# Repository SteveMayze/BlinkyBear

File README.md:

# BlinkyBear
This is a small case-study in creating a custom board layout with KiCad. A small writeup can be found on my  [Contextual Electronics Build Log](https://forum.contextualelectronics.com/t/steves-build-log/28/62) until I get around to writing things up better here.

The BOM is simple enough, 

* 1 x CR 1216, CR 1220 Horizontal Surface mount battery holder
* 1 x Mini Slide Switch e.g. SK12C0405SG1.5RT
* 2 x 1556769 RGB LED (EAN: 2050004827125) or similar
* 1 x Brooche pin, 15mm

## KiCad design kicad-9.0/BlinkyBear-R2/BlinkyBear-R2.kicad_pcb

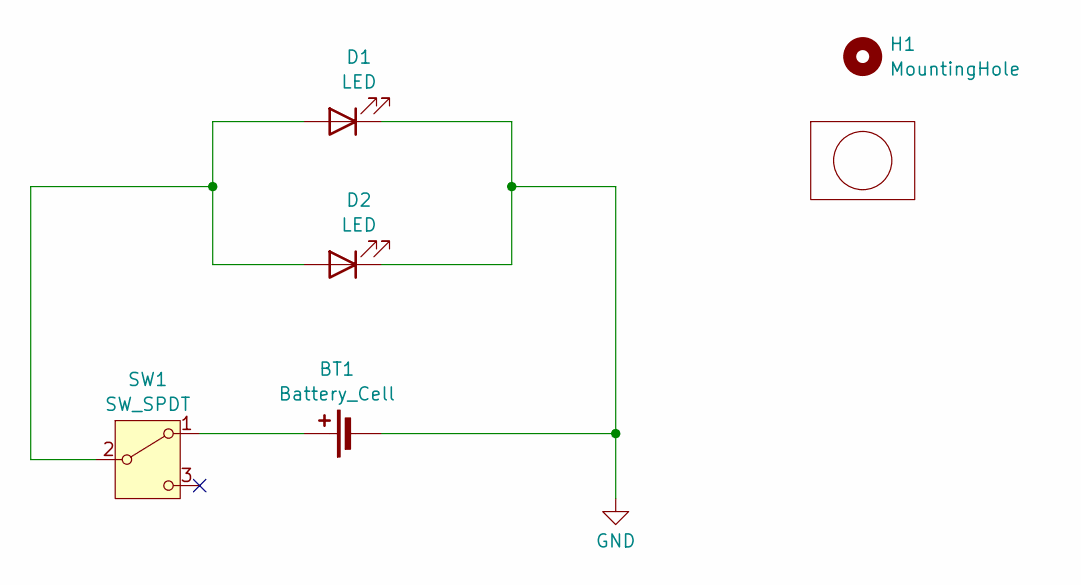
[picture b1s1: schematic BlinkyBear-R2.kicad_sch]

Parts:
BT1: Battery_Cell; CR1220_Halter
D1, D2: LED; LED_D5.0mm
H1: MountingHole; Butterfly-Pin
Lg1: logo; ZAM_LOGO_440
SW1: SW_SPDT; SW_SPDT_PCM12

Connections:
GND: BT1.2 (-), D1.1 (K), D2.1 (K)
unnamed: BT1.1 (+), SW1.1 (A)
unnamed: D1.2 (A), D2.2 (A), SW1.2 (B)

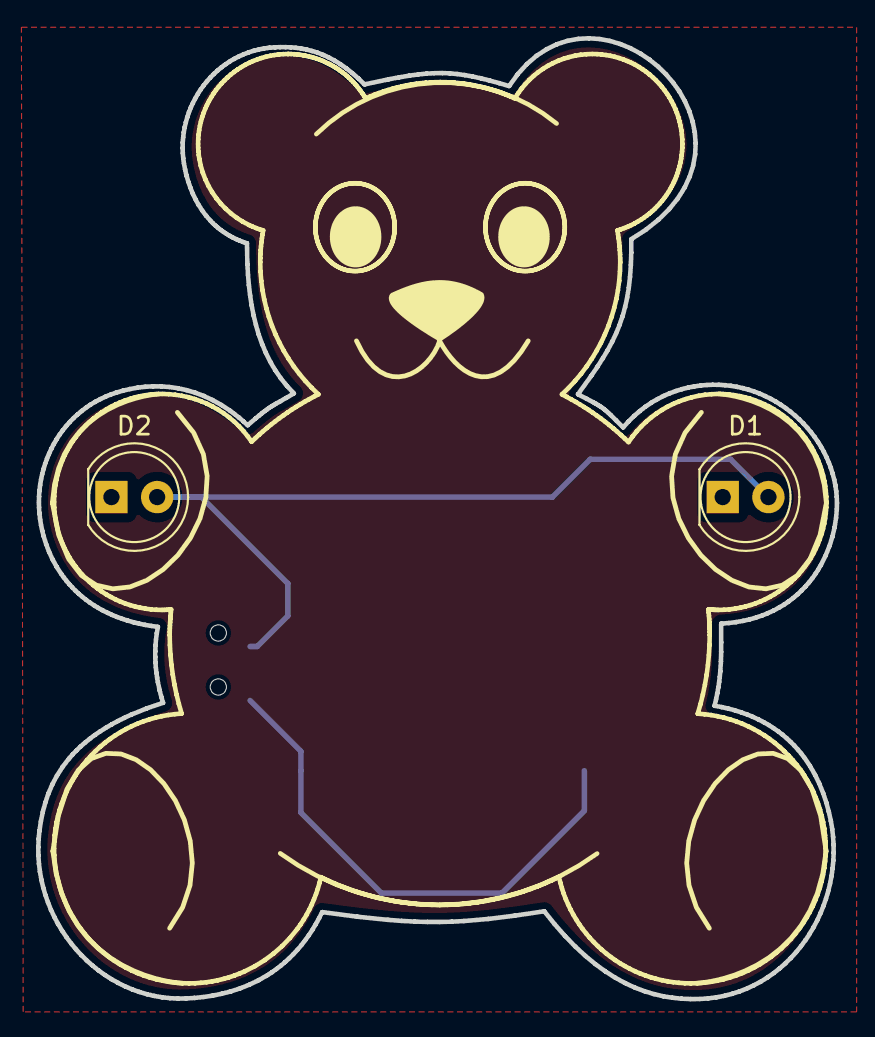
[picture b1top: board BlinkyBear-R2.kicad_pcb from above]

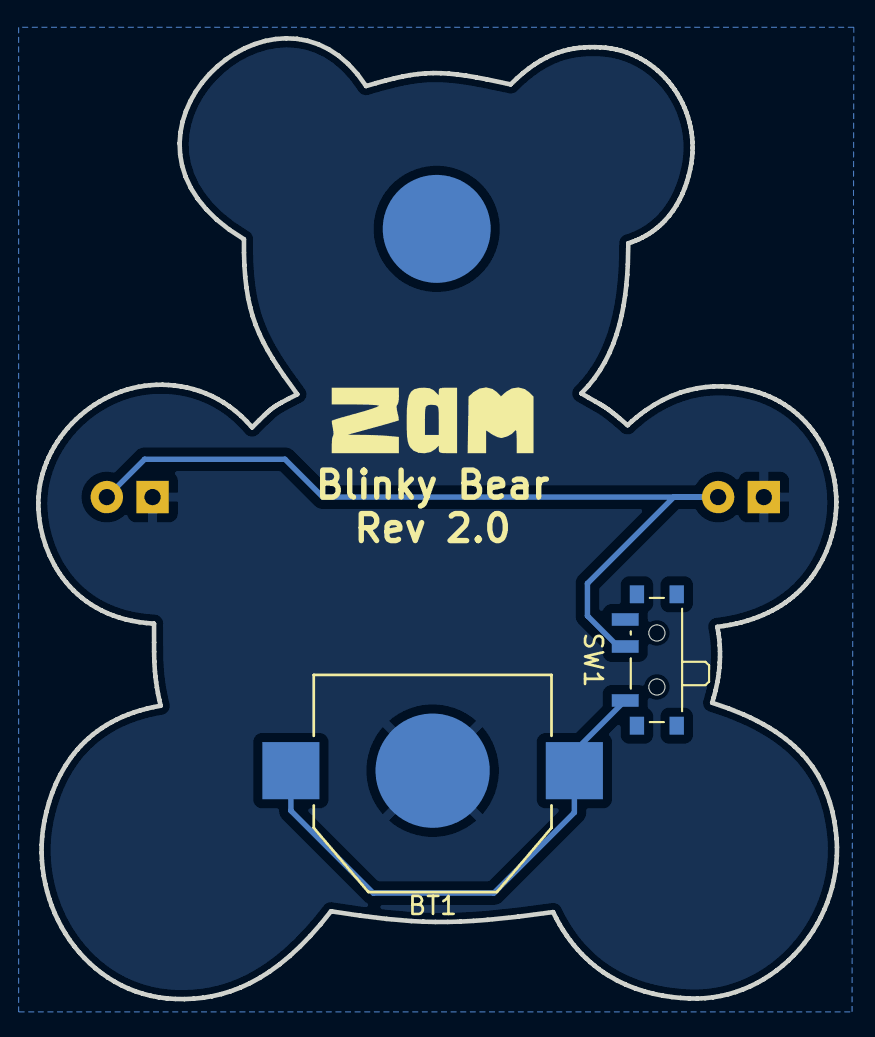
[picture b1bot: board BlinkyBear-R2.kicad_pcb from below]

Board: 2 copper layers, 44.4 x 53.4 mm, 6 parts (4 on the bottom side), 3 nets.

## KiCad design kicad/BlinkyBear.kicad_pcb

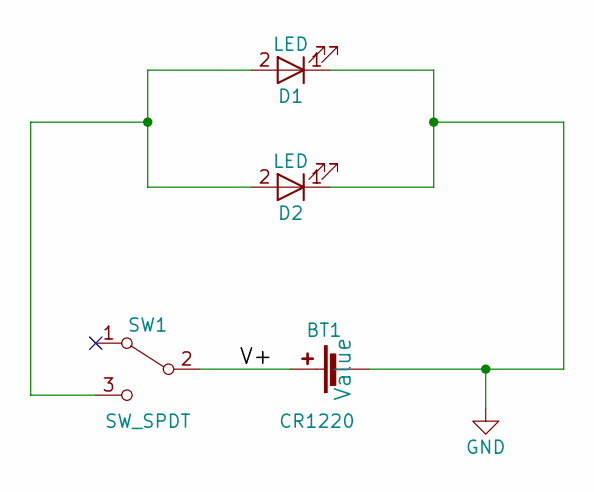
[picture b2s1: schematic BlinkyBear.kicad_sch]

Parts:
BT1: CR1220; CR1220_Halter; MPN 651317 - 62
D1, D2: LED; LED_D4.0mm; MPN LED 5-RGB2-L
SW1: SW_SPDT; SW_SPDT_PCM12; MPN 248762 - 62

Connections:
/V+: BT1.1 (+), SW1.2 (B)
GND: BT1.2 (-), D1.1 (K), D2.1 (K)
unnamed: D1.2 (A), D2.2 (A), SW1.3 (C)

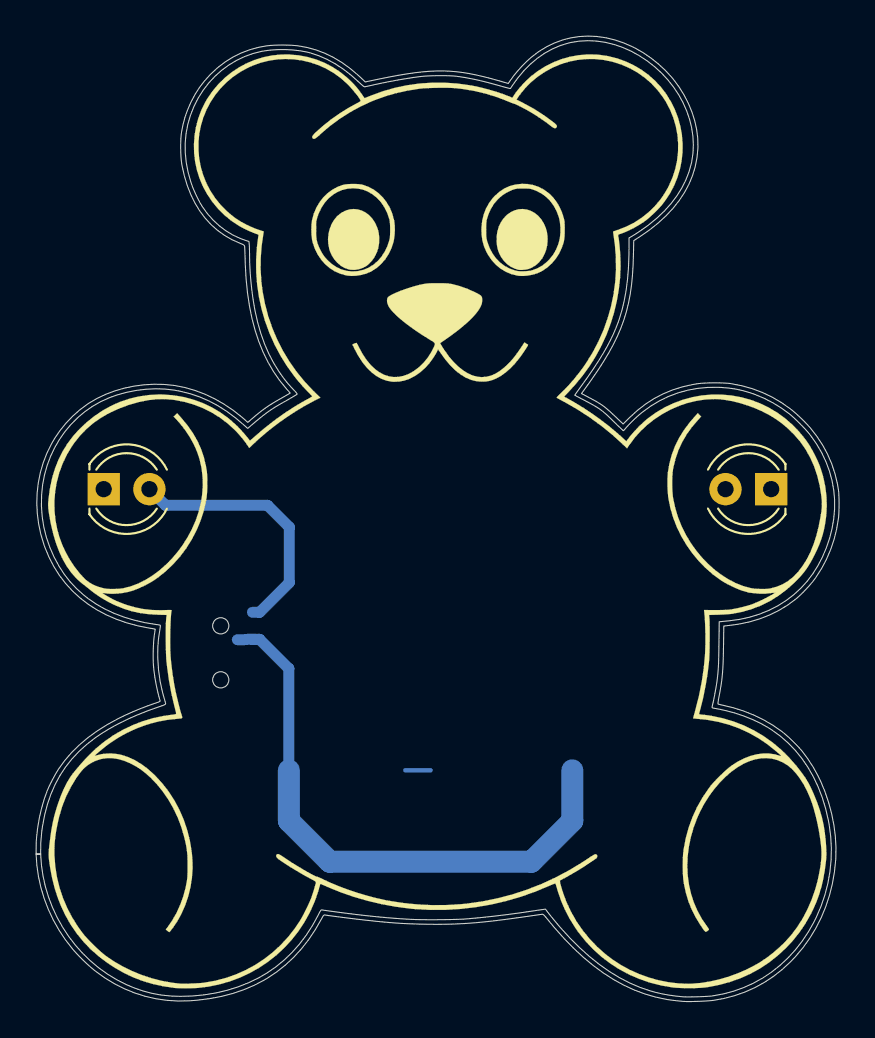
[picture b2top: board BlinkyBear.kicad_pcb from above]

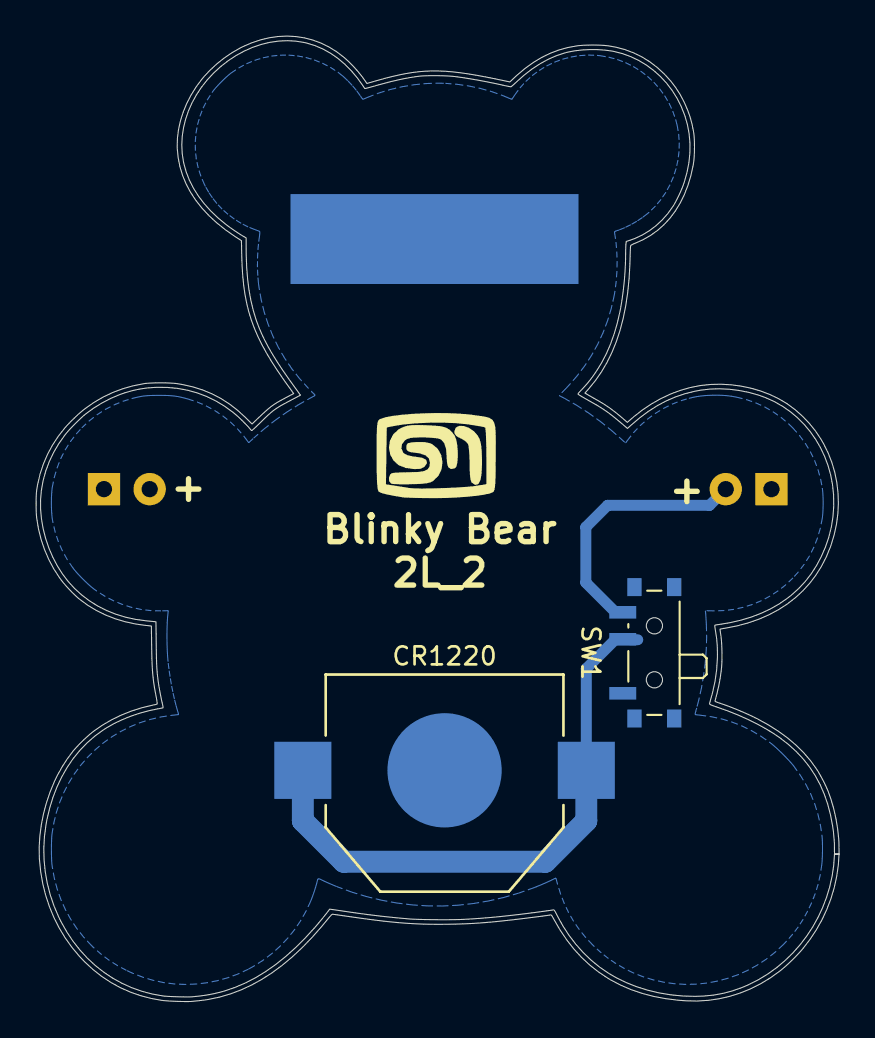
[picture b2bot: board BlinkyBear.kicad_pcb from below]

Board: 2 copper layers, 44.6 x 53.6 mm, 5 parts (2 on the bottom side), 3 nets.

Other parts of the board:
Bear***: LOGO; BlinkyBear_outline

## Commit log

2018-05-06 Initial checkin
2018-05-28 Created the README.md with a basic BOM.
2018-05-28 Corrected the BOM list to format properly.
2021-11-21 Updates and adds a BOM
2021-12-02 Adds documentation
2025-02-08 Refreshed to KiCad 8
2025-02-08 Rescuded the SVG files
2025-11-22 Updated the design to use the new 9.0 image import features
